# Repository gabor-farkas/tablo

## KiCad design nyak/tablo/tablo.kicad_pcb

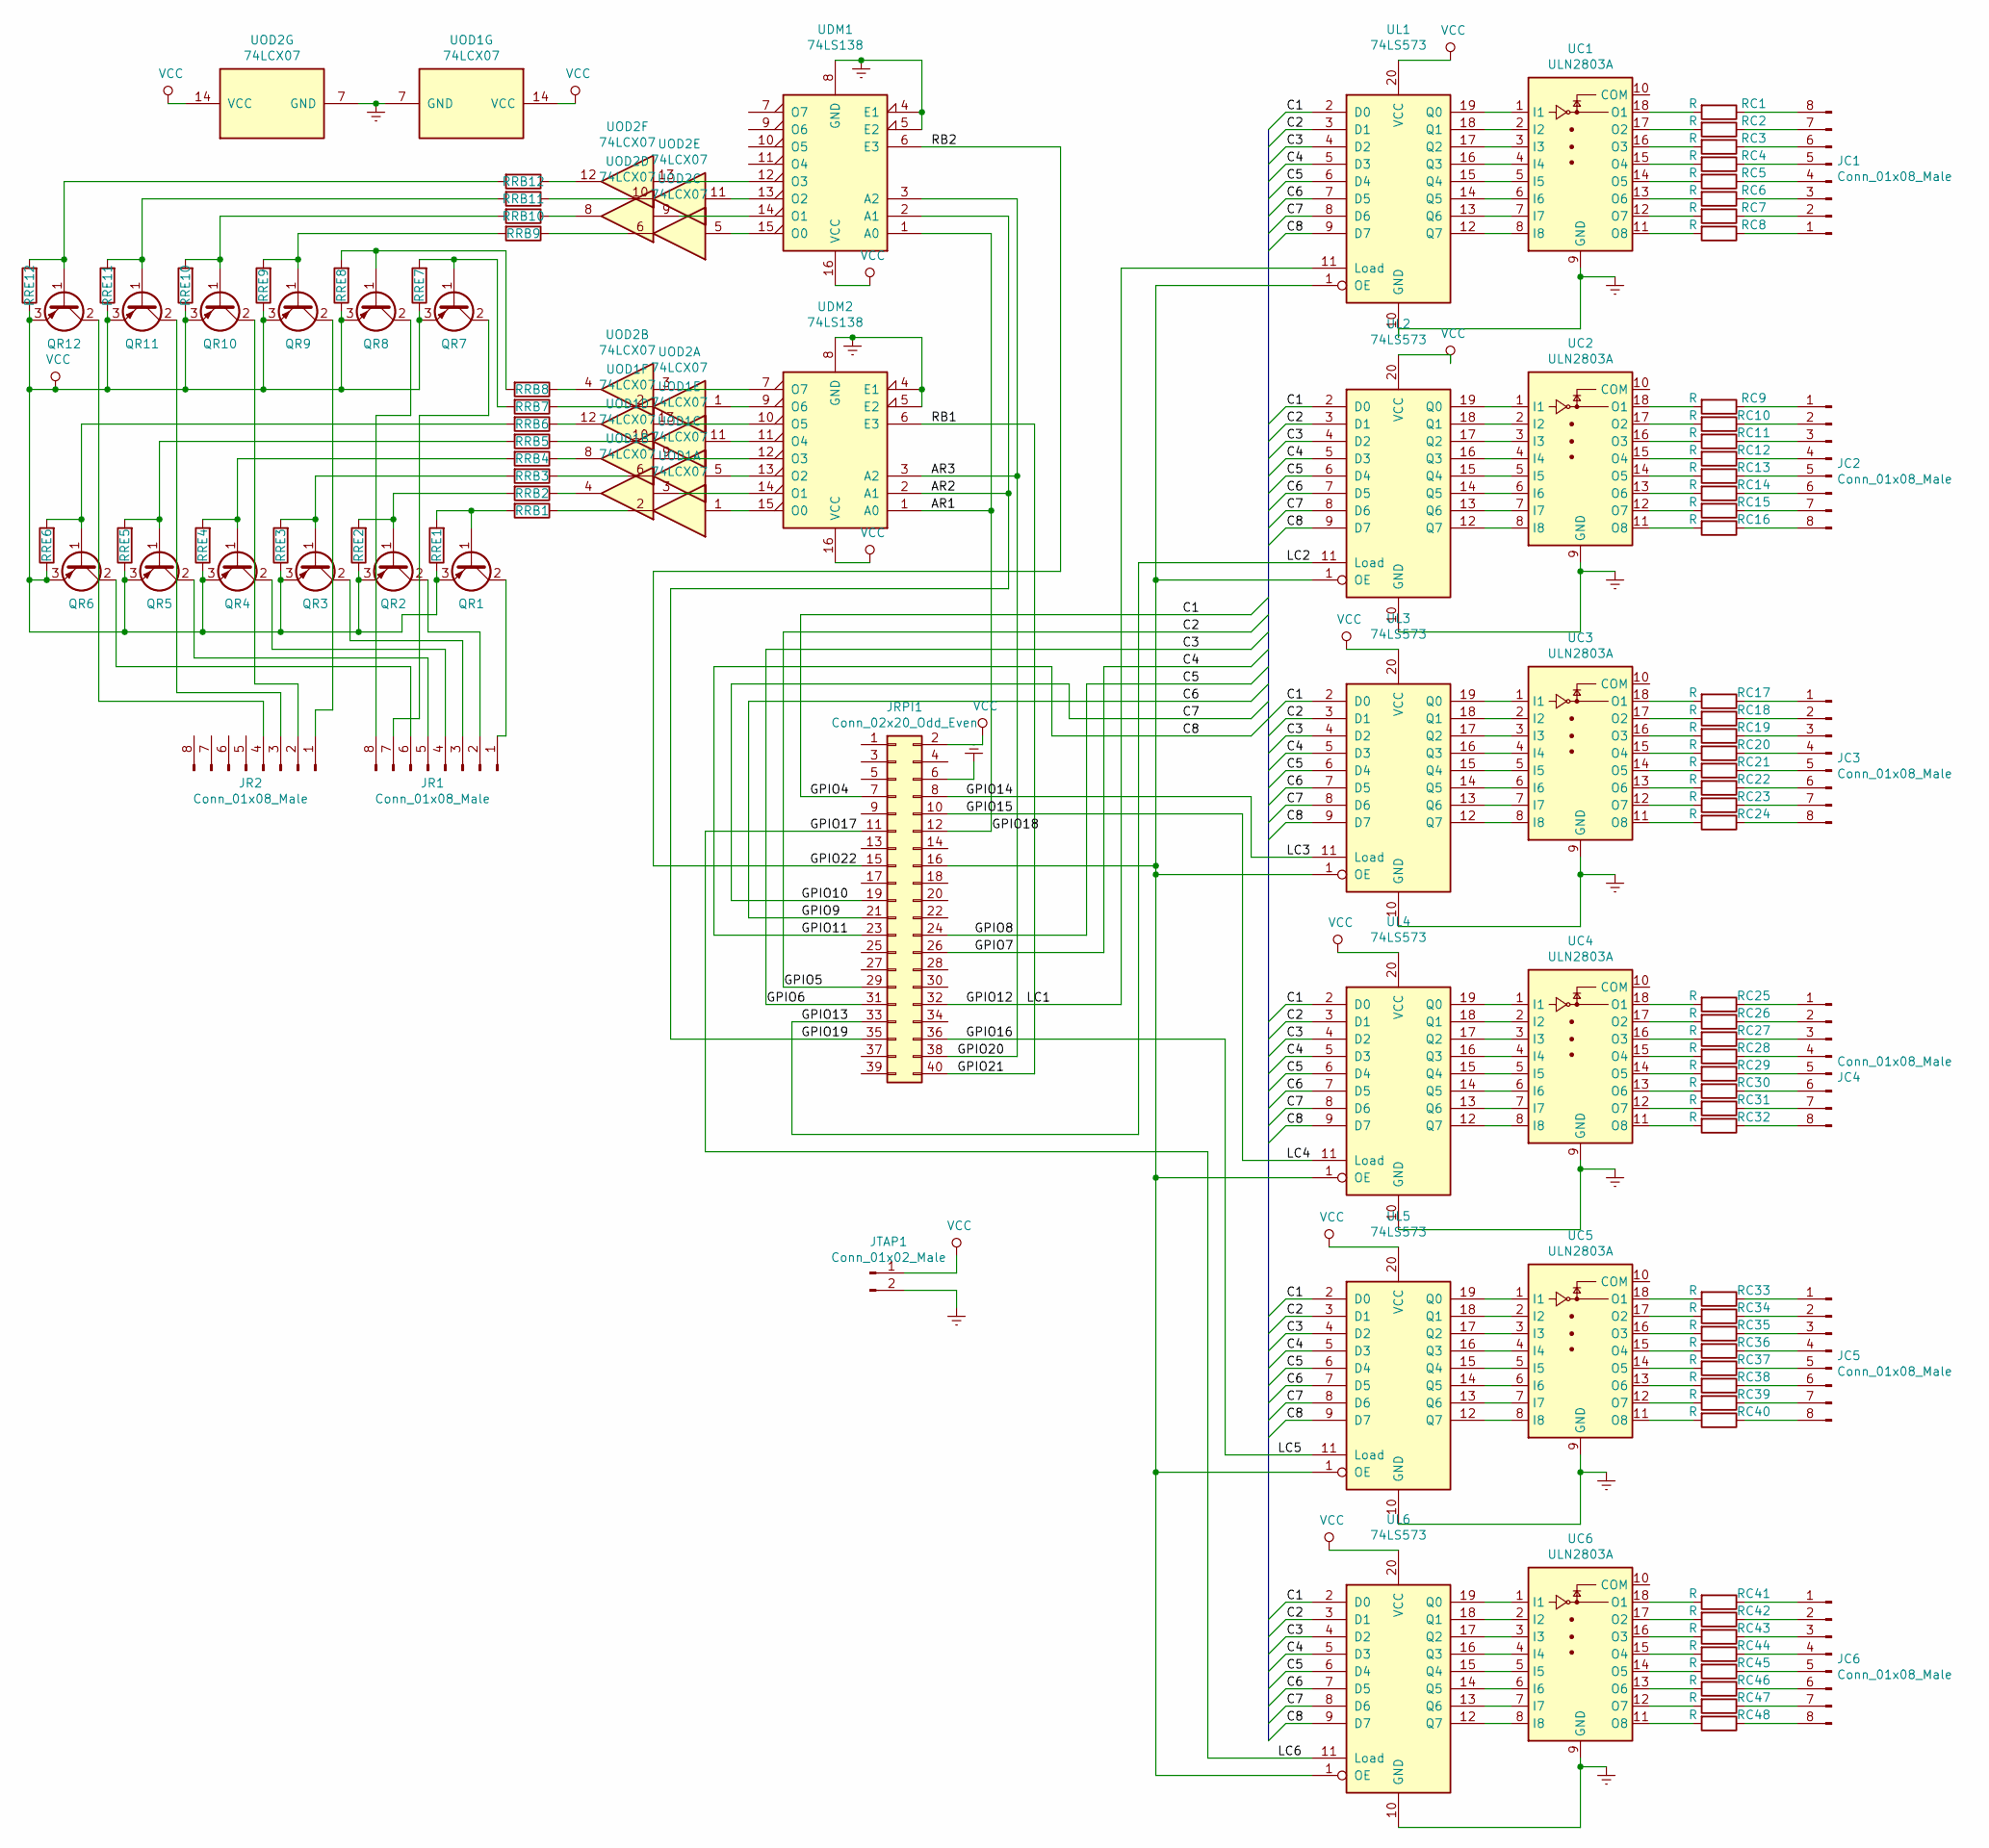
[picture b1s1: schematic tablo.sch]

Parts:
JC1, JC2, JC3, JC4, JC5, JC6: Conn_01x08_Male; PinHeader_1x08_P2.54mm_Vertical
JR1, JR2: Conn_01x08_Male; PinHeader_1x08_P2.54mm_Vertical
JRPI1: Conn_02x20_Odd_Even; PinHeader_2x20_P2.54mm_Vertical
JTAP1: Conn_01x02_Male; PinHeader_1x02_P2.54mm_Vertical
QR1, QR2, QR3, QR4, QR5, QR6, QR7, QR8, QR9, QR10, QR11, QR12: BD250; TO-220-3_Vertical
RC1, RC2, RC3, RC4, RC5, RC6, RC7, RC8, RC9, RC10, RC11, RC12, RC13, RC14, RC15, RC16, RC17, RC18, RC19, RC20, RC21, RC22, RC23, RC24, RC25, RC26, RC27, RC28, RC29, RC30, RC31, RC32, RC33, RC34, RC35, RC36, RC37, RC38, RC39, RC40, RC41, RC42, RC43, RC44, RC45, RC46, RC47, RC48: R; R_Axial_DIN0207_L6.3mm_D2.5mm_P7.62mm_Horizontal
RRB1, RRB2, RRB3, RRB4, RRB5, RRB6, RRB7, RRB8, RRB9, RRB10, RRB11, RRB12: R; R_Axial_DIN0207_L6.3mm_D2.5mm_P7.62mm_Horizontal
RRE1, RRE2, RRE3, RRE4, RRE5, RRE6, RRE7, RRE8, RRE9, RRE10, RRE11, RRE12: R; R_Axial_DIN0207_L6.3mm_D2.5mm_P7.62mm_Horizontal
UC1, UC2, UC3, UC4, UC5, UC6: ULN2803A; DIP-18_W7.62mm
UDM1, UDM2: 74LS138; DIP-16_W7.62mm
UL1, UL2, UL3, UL4, UL5, UL6: 74LS573; DIP-20_W7.62mm
UOD1, UOD2: 74LCX07; DIP-14_W7.62mm

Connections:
/AR1: JRPI1.12, UDM1.1 (A0), UDM2.1 (A0)
/AR2: JRPI1.35, UDM1.2 (A1), UDM2.2 (A1)
/AR3: JRPI1.38, UDM1.3 (A2), UDM2.3 (A2)
/C1: JRPI1.7, UL1.2 (D0), UL2.2 (D0), UL3.2 (D0), UL4.2 (D0), UL5.2 (D0), UL6.2 (D0)
/C2: JRPI1.29, UL1.3 (D1), UL2.3 (D1), UL3.3 (D1), UL4.3 (D1), UL5.3 (D1), UL6.3 (D1)
/C3: JRPI1.31, UL1.4 (D2), UL2.4 (D2), UL3.4 (D2), UL4.4 (D2), UL5.4 (D2), UL6.4 (D2)
/C4: JRPI1.26, UL1.5 (D3), UL2.5 (D3), UL3.5 (D3), UL4.5 (D3), UL5.5 (D3), UL6.5 (D3)
/C5: JRPI1.24, UL1.6 (D4), UL2.6 (D4), UL3.6 (D4), UL4.6 (D4), UL5.6 (D4), UL6.6 (D4)
/C6: JRPI1.21, UL1.7 (D5), UL2.7 (D5), UL3.7 (D5), UL4.7 (D5), UL5.7 (D5), UL6.7 (D5)
/C7: JRPI1.19, UL1.8 (D6), UL2.8 (D6), UL3.8 (D6), UL4.8 (D6), UL5.8 (D6), UL6.8 (D6)
/C8: JRPI1.23, UL1.9 (D7), UL2.9 (D7), UL3.9 (D7), UL4.9 (D7), UL5.9 (D7), UL6.9 (D7)
/GPIO12: JRPI1.32, UL1.11 (Load)
/GPIO13: JRPI1.33, UL2.11 (Load)
/GPIO14: JRPI1.8, UL3.11 (Load)
/GPIO15: JRPI1.10, UL4.11 (Load)
/GPIO16: JRPI1.36, UL5.11 (Load)
/GPIO17: JRPI1.11, UL6.11 (Load)
/GPIO21: JRPI1.40, UDM2.6 (E3)
/GPIO22: JRPI1.15, UDM1.6 (E3)
Earth: JRPI1.6, JTAP1.2, UC1.9 (GND), UC2.9 (GND), UC3.9 (GND), UC4.9 (GND), UC5.9 (GND), UC6.9 (GND), UDM1.4 (E1), UDM1.5 (E2), UDM1.8 (GND), UDM2.4 (E1), UDM2.5 (E2), UDM2.8 (GND), UL1.10 (GND), UL2.10 (GND), UL3.10 (GND), UL4.10 (GND), UL5.10 (GND), UL6.10 (GND), UOD1.7 (GND), UOD2.7 (GND)
unnamed: JC1.1, RC8.1
unnamed: JC1.2, RC7.1
unnamed: JC1.3, RC6.1
unnamed: JC1.4, RC5.1
unnamed: JC1.5, RC4.1
unnamed: JC1.6, RC3.1
unnamed: JC1.7, RC2.1
unnamed: JC1.8, RC1.1
unnamed: JC2.1, RC9.1
unnamed: JC2.2, RC10.1
unnamed: JC2.3, RC11.1
unnamed: JC2.4, RC12.1
unnamed: JC2.5, RC13.1
unnamed: JC2.6, RC14.1
unnamed: JC2.7, RC15.1
unnamed: JC2.8, RC16.1
unnamed: JC3.1, RC17.1
unnamed: JC3.2, RC18.1
unnamed: JC3.3, RC19.1
unnamed: JC3.4, RC20.1
unnamed: JC3.5, RC21.1
unnamed: JC3.6, RC22.1
unnamed: JC3.7, RC23.1
unnamed: JC3.8, RC24.1
unnamed: JC4.1, RC25.1
unnamed: JC4.2, RC26.1
unnamed: JC4.3, RC27.1
unnamed: JC4.4, RC28.1
unnamed: JC4.5, RC29.1
unnamed: JC4.6, RC30.1
unnamed: JC4.7, RC31.1
unnamed: JC4.8, RC32.1
unnamed: JC5.1, RC33.1
unnamed: JC5.2, RC34.1
unnamed: JC5.3, RC35.1
unnamed: JC5.4, RC36.1
unnamed: JC5.5, RC37.1
unnamed: JC5.6, RC38.1
unnamed: JC5.7, RC39.1
unnamed: JC5.8, RC40.1
unnamed: JC6.1, RC41.1
unnamed: JC6.2, RC42.1
unnamed: JC6.3, RC43.1
unnamed: JC6.4, RC44.1
unnamed: JC6.5, RC45.1
unnamed: JC6.6, RC46.1
unnamed: JC6.7, RC47.1
unnamed: JC6.8, RC48.1
unnamed: JR1.1, QR1.2 (C)
unnamed: JR1.2, QR2.2 (C)
unnamed: JR1.3, QR3.2 (C)
unnamed: JR1.4, QR4.2 (C)
unnamed: JR1.5, QR5.2 (C)
unnamed: JR1.6, QR6.2 (C)
unnamed: JR1.7, QR7.2 (C)
unnamed: JR1.8, QR8.2 (C)
unnamed: JR2.1, QR9.2 (C)
unnamed: JR2.2, QR10.2 (C)
unnamed: JR2.3, QR11.2 (C)
unnamed: JR2.4, QR12.2 (C)
unnamed: JRPI1.16, UL1.1 (OE), UL2.1 (OE), UL3.1 (OE), UL4.1 (OE), UL5.1 (OE), UL6.1 (OE)
unnamed: QR1.1 (B), RRB1.2, RRE1.2
unnamed: QR2.1 (B), RRB2.2, RRE2.2
unnamed: QR3.1 (B), RRB3.2, RRE3.2
unnamed: QR4.1 (B), RRB4.2, RRE4.2
unnamed: QR5.1 (B), RRB5.2, RRE5.2
unnamed: QR6.1 (B), RRB6.2, RRE6.2
unnamed: QR7.1 (B), RRB7.2, RRE7.2
unnamed: QR8.1 (B), RRB8.2, RRE8.2
unnamed: QR9.1 (B), RRB9.2, RRE9.2
unnamed: QR10.1 (B), RRB10.2, RRE10.2
unnamed: QR11.1 (B), RRB11.2, RRE11.2
unnamed: QR12.1 (B), RRB12.2, RRE12.2
unnamed: RC1.2, UC1.18 (O1)
unnamed: RC2.2, UC1.17 (O2)
unnamed: RC3.2, UC1.16 (O3)
unnamed: RC4.2, UC1.15 (O4)
unnamed: RC5.2, UC1.14 (O5)
unnamed: RC6.2, UC1.13 (O6)
unnamed: RC7.2, UC1.12 (O7)
unnamed: RC8.2, UC1.11 (O8)
unnamed: RC9.2, UC2.18 (O1)
unnamed: RC10.2, UC2.17 (O2)
unnamed: RC11.2, UC2.16 (O3)
unnamed: RC12.2, UC2.15 (O4)
unnamed: RC13.2, UC2.14 (O5)
unnamed: RC14.2, UC2.13 (O6)
unnamed: RC15.2, UC2.12 (O7)
unnamed: RC16.2, UC2.11 (O8)
unnamed: RC17.2, UC3.18 (O1)
unnamed: RC18.2, UC3.17 (O2)
unnamed: RC19.2, UC3.16 (O3)
unnamed: RC20.2, UC3.15 (O4)
unnamed: RC21.2, UC3.14 (O5)
unnamed: RC22.2, UC3.13 (O6)
unnamed: RC23.2, UC3.12 (O7)
unnamed: RC24.2, UC3.11 (O8)
unnamed: RC25.2, UC4.18 (O1)
unnamed: RC26.2, UC4.17 (O2)
unnamed: RC27.2, UC4.16 (O3)
unnamed: RC28.2, UC4.15 (O4)
unnamed: RC29.2, UC4.14 (O5)
unnamed: RC30.2, UC4.13 (O6)
unnamed: RC31.2, UC4.12 (O7)
unnamed: RC32.2, UC4.11 (O8)
unnamed: RC33.2, UC5.18 (O1)
unnamed: RC34.2, UC5.17 (O2)
unnamed: RC35.2, UC5.16 (O3)
unnamed: RC36.2, UC5.15 (O4)
unnamed: RC37.2, UC5.14 (O5)
unnamed: RC38.2, UC5.13 (O6)
unnamed: RC39.2, UC5.12 (O7)
unnamed: RC40.2, UC5.11 (O8)
unnamed: RC41.2, UC6.18 (O1)
unnamed: RC42.2, UC6.17 (O2)
unnamed: RC43.2, UC6.16 (O3)
unnamed: RC44.2, UC6.15 (O4)
unnamed: RC45.2, UC6.14 (O5)
unnamed: RC46.2, UC6.13 (O6)
unnamed: RC47.2, UC6.12 (O7)
unnamed: RC48.2, UC6.11 (O8)
unnamed: RRB1.1, UOD1.2
unnamed: RRB2.1, UOD1.4
unnamed: RRB3.1, UOD1.6
unnamed: RRB4.1, UOD1.8
unnamed: RRB5.1, UOD1.10
unnamed: RRB6.1, UOD1.12
unnamed: RRB7.1, UOD2.2
unnamed: RRB8.1, UOD2.4
unnamed: RRB9.1, UOD2.6
unnamed: RRB10.1, UOD2.8
unnamed: RRB11.1, UOD2.10
unnamed: RRB12.1, UOD2.12
unnamed: UC1.1 (I1), UL1.19 (Q0)
unnamed: UC1.2 (I2), UL1.18 (Q1)
unnamed: UC1.3 (I3), UL1.17 (Q2)
unnamed: UC1.4 (I4), UL1.16 (Q3)
unnamed: UC1.5 (I5), UL1.15 (Q4)
unnamed: UC1.6 (I6), UL1.14 (Q5)
unnamed: UC1.7 (I7), UL1.13 (Q6)
unnamed: UC1.8 (I8), UL1.12 (Q7)
unnamed: UC2.1 (I1), UL2.19 (Q0)
unnamed: UC2.2 (I2), UL2.18 (Q1)
unnamed: UC2.3 (I3), UL2.17 (Q2)
unnamed: UC2.4 (I4), UL2.16 (Q3)
unnamed: UC2.5 (I5), UL2.15 (Q4)
unnamed: UC2.6 (I6), UL2.14 (Q5)
unnamed: UC2.7 (I7), UL2.13 (Q6)
unnamed: UC2.8 (I8), UL2.12 (Q7)
unnamed: UC3.1 (I1), UL3.19 (Q0)
unnamed: UC3.2 (I2), UL3.18 (Q1)
unnamed: UC3.3 (I3), UL3.17 (Q2)
unnamed: UC3.4 (I4), UL3.16 (Q3)
unnamed: UC3.5 (I5), UL3.15 (Q4)
unnamed: UC3.6 (I6), UL3.14 (Q5)
unnamed: UC3.7 (I7), UL3.13 (Q6)
unnamed: UC3.8 (I8), UL3.12 (Q7)
unnamed: UC4.1 (I1), UL4.19 (Q0)
unnamed: UC4.2 (I2), UL4.18 (Q1)
unnamed: UC4.3 (I3), UL4.17 (Q2)
unnamed: UC4.4 (I4), UL4.16 (Q3)
unnamed: UC4.5 (I5), UL4.15 (Q4)
unnamed: UC4.6 (I6), UL4.14 (Q5)
unnamed: UC4.7 (I7), UL4.13 (Q6)
unnamed: UC4.8 (I8), UL4.12 (Q7)
unnamed: UC5.1 (I1), UL5.19 (Q0)
unnamed: UC5.2 (I2), UL5.18 (Q1)
unnamed: UC5.3 (I3), UL5.17 (Q2)
unnamed: UC5.4 (I4), UL5.16 (Q3)
unnamed: UC5.5 (I5), UL5.15 (Q4)
unnamed: UC5.6 (I6), UL5.14 (Q5)
unnamed: UC5.7 (I7), UL5.13 (Q6)
unnamed: UC5.8 (I8), UL5.12 (Q7)
unnamed: UC6.1 (I1), UL6.19 (Q0)
unnamed: UC6.2 (I2), UL6.18 (Q1)
unnamed: UC6.3 (I3), UL6.17 (Q2)
unnamed: UC6.4 (I4), UL6.16 (Q3)
unnamed: UC6.5 (I5), UL6.15 (Q4)
unnamed: UC6.6 (I6), UL6.14 (Q5)
unnamed: UC6.7 (I7), UL6.13 (Q6)
unnamed: UC6.8 (I8), UL6.12 (Q7)
unnamed: UDM1.12 (O3), UOD2.13
unnamed: UDM1.13 (O2), UOD2.11
unnamed: UDM1.14 (O1), UOD2.9
unnamed: UDM1.15 (O0), UOD2.5
unnamed: UDM2.7 (O7), UOD2.3
unnamed: UDM2.9 (O6), UOD2.1
unnamed: UDM2.10 (O5), UOD1.13
unnamed: UDM2.11 (O4), UOD1.11
unnamed: UDM2.12 (O3), UOD1.9
unnamed: UDM2.13 (O2), UOD1.5
unnamed: UDM2.14 (O1), UOD1.3
unnamed: UDM2.15 (O0), UOD1.1
VCC: JRPI1.2, JTAP1.1, QR1.3 (E), QR2.3 (E), QR3.3 (E), QR4.3 (E), QR5.3 (E), QR6.3 (E), QR7.3 (E), QR8.3 (E), QR9.3 (E), QR10.3 (E), QR11.3 (E), QR12.3 (E), RRE1.1, RRE2.1, RRE3.1, RRE4.1, RRE5.1, RRE6.1, RRE7.1, RRE8.1, RRE9.1, RRE10.1, RRE11.1, RRE12.1, UDM1.16 (VCC), UDM2.16 (VCC), UL1.20 (VCC), UL2.20 (VCC), UL3.20 (VCC), UL4.20 (VCC), UL5.20 (VCC), UL6.20 (VCC), UOD1.14 (VCC), UOD2.14 (VCC)

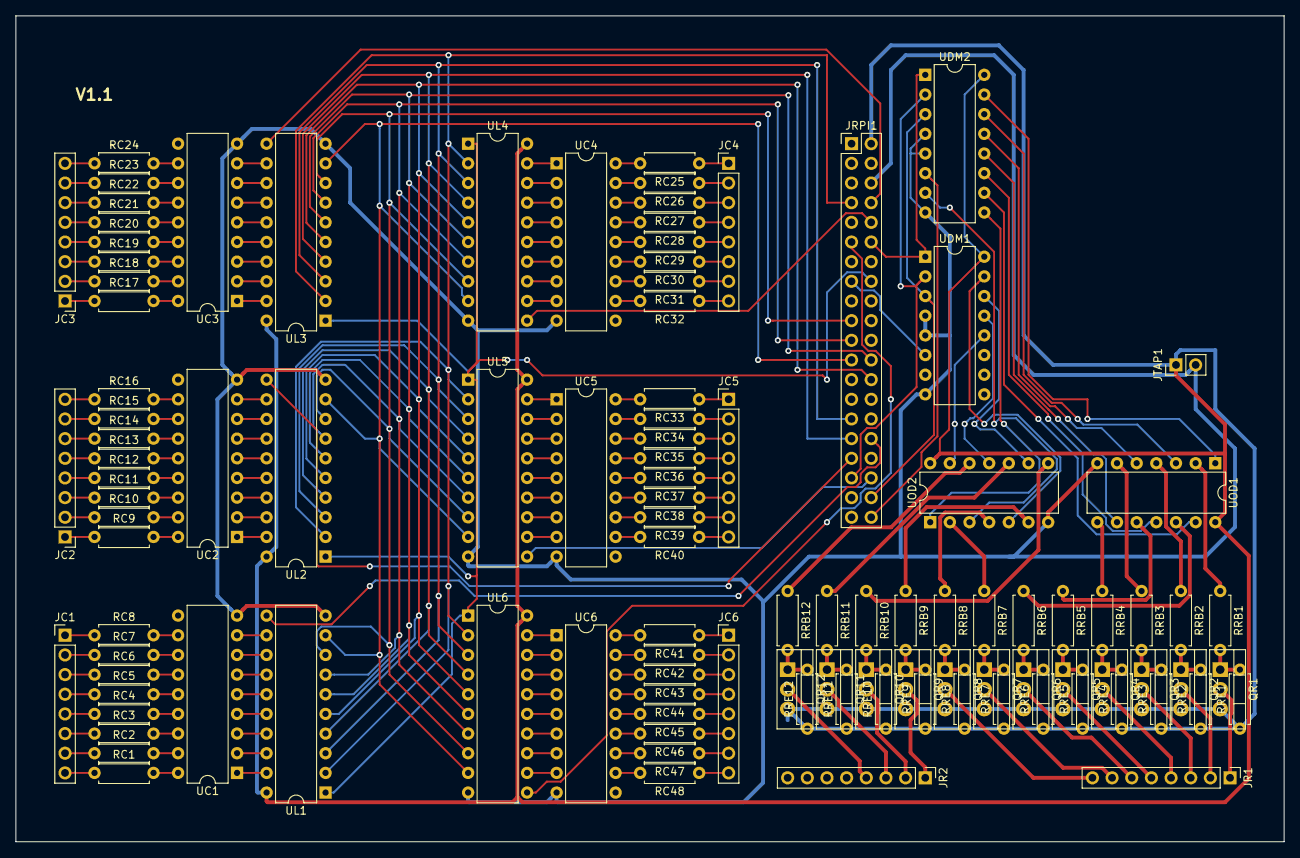
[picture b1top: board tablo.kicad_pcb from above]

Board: 2 copper layers, 163.8 x 106.7 mm, 110 parts (0 on the bottom side), 214 nets.

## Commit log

2019-10-22 more wiring
2019-10-23 footprints added
2019-10-24 more tracks
2019-11-01 more pcb
2019-11-02 seems to be finished
2019-11-05 updated rpi gpio connector footprint
2019-11-05 initial gerber files
2020-01-02 Fixed row switch PNP transistor emitter connection from GND to VCC
2020-01-02 Updated resistor footprints to have 0.8mm holes instead of 0.7
